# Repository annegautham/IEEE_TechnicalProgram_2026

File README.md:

View this project on [CADLAB.io](https://cadlab.io/project/30137). 

# IEEE_TechnicalProgram_2026

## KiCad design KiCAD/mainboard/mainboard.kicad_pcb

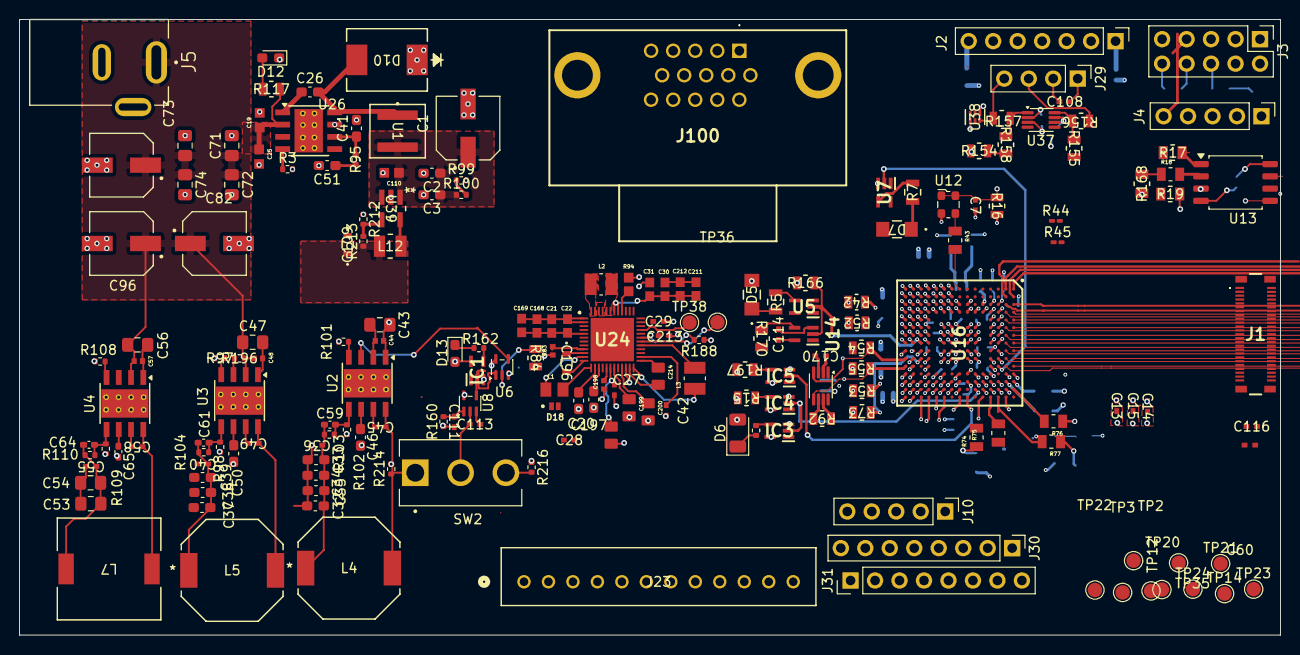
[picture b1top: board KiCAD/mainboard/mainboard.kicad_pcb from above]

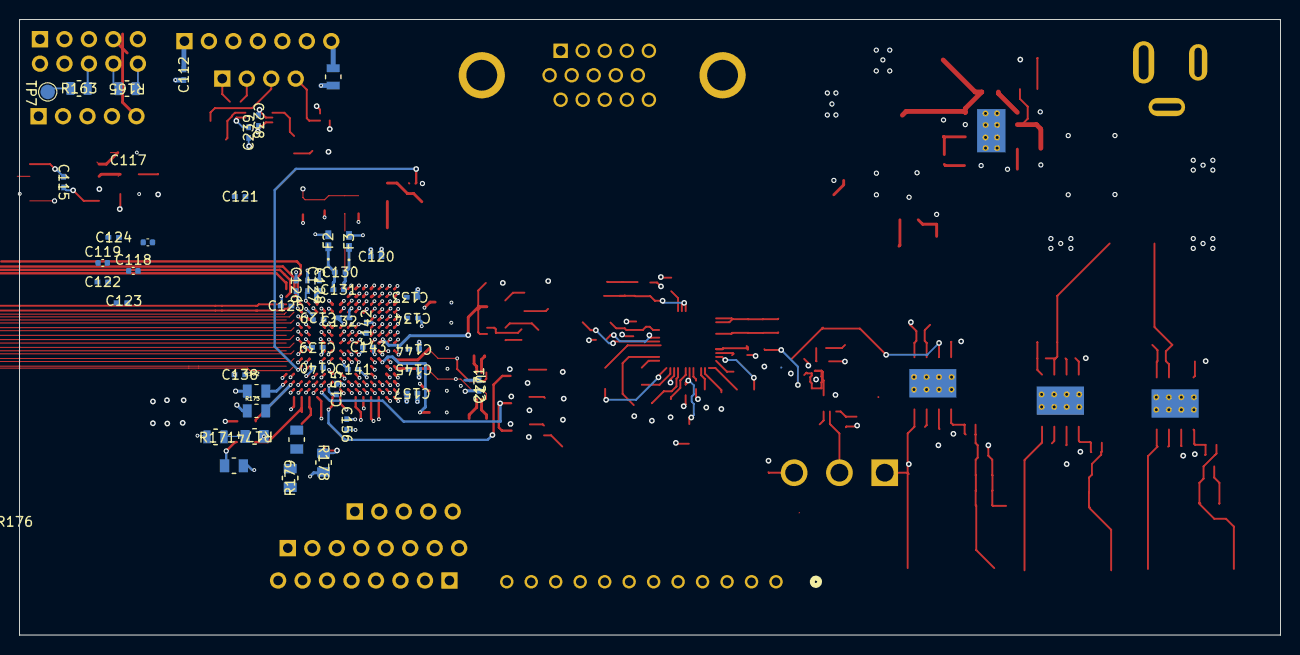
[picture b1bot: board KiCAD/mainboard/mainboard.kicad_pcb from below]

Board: 10 copper layers, 130.9 x 63.9 mm, 240 parts (48 on the bottom side), 171 nets.

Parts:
C1, C82, C83, C96: 100 uF; CAP_EEEFT1V101AP
C2, C3, C41: 12pF; C_0603_1608Metric_Pad1.08x0.95mm_HandSolder
C7, C13, C14, C15, C27, C29, C42, C116, C120, C121, C122, C123, C124, C125, C126, C128, C129, C130, C131, C132, C133, C134, C139, C140, C141, C142, C143, C144, C145, C155, C156, C157, C213, C238, C239: 100nF; CAP_CL05_SAM
C19, C25, C110: 4.7uF; GRM188C81E475KE11D
C20, C197: 220nF; C_0603_1608Metric_Pad1.08x0.95mm_HandSolder
C21, C22, C30, C31, C168, C169, C211, C212: 22uF; CAPC1608X100N
C26: 100nF; C_0603_1608Metric_Pad1.08x0.95mm_HandSolder
C28: 4.7uF; CAP_CL05_SAM
C32, C33, C34, C35, C37, C38, C39: 22uF; C_0603_1608Metric_Pad1.08x0.95mm_HandSolder
C36, C40, C45, C49, C55, C58, C60, C111, C113: 100nF; ul_CL05B104KO5NNNC
C43, C47, C56: 4.7uF; C_0805_2012Metric_Pad1.18x1.45mm_HandSolder
C44, C48, C57, C198: 220nF; GRM155R6YA224KE01D
C46, C50: 1uF; C_0603_1608Metric_Pad1.08x0.95mm_HandSolder
C51: 100pF; C_0603_1608Metric_Pad1.08x0.95mm_HandSolder
C53, C54: 10uF; C_0805_2012Metric_Pad1.18x1.45mm_HandSolder
C59: 4.7pF; C_0402_1005Metric_Pad0.74x0.62mm_HandSolder
C61: 10pF; C_0402_1005Metric_Pad0.74x0.62mm_HandSolder
C64: 18pF; C_0402_1005Metric_Pad0.74x0.62mm_HandSolder
C65: 1uF; C_0402_1005Metric_Pad0.74x0.62mm_HandSolder
C71, C72, C73, C74: 10 uF; C_0805_2012Metric_Pad1.18x1.45mm_HandSolder
C108, C112, C114, C115, C127, C138, C170, C171: 100n; CAP_CL05_SAM
C109, C196: 10uF; C1608X5R1A106M080AC
C117, C118, C119: 220n; C_0402_1005Metric
C199: 2.2uF; CAPC2012X135N
C200, C201, C214: 1uF; CAPC2012X135N
D5, D7: SML-LX1206SIC-TR; LED_SML-LX1206SIC-TR_LUM-M
D6: LED; LED_1206_3216Metric
D10: B560C; SMC_DIO
D12, D13: LED; LED_0603_1608Metric_Pad1.05x0.95mm_HandSolder
D18: D_Schottky; DIO_PESD5V0S1UL_315
F2, F3: 1500mA; BLM15P_FBD-M
IC1, IC3: SN74AUP1G06DCKR; SOT65P210X110-5N
IC4, IC5: SN74AUP1G07DCKR; SOT65P210X110-5N
J1: AXT550124
J2: Conn_01x07_Pin; PinHeader_1x07_P2.54mm_Vertical
J3: Conn_02x05_Odd_Even; PinHeader_2x05_P2.54mm_Vertical
J4, J10: Conn_01x05_Pin; PinHeader_1x05_P2.54mm_Vertical
J5: EJ508B; MPD_EJ508B
J23: B12B-XH-ALFSN; B12B-XH-A-LF-SN-
J29: Conn_01x04_Pin; PinHeader_1x04_P2.54mm_Vertical
J30, J31: Conn_01x08_Pin; PinHeader_1x08_P2.54mm_Vertical
J100: AHDF15A-KG-TAXB; AHDF15AKGTAXB
L1: 10uH; INDC2012X100N
L2, L3: 2.2uH; INDC2520X100N
L4, L5: SRU1038-3R5Y; IND_BOURNS_SRU1038
L7: DR1040-5R2-R; DR1040
L12: LQM2HPN2R2MG0L; IND_LQM2HPN2R2MG0L_MUR
R3, R212: 78.7k; R_0402_1005Metric
R5, R7: 100; RES_CRCW_0805
R6: 150; R_0402_1005Metric
R15, R84, R92, R155, R158, R163, R164, R165, R166, R170, R197: 10k; STA_RMCF0805_STP
R16, R154, R156, R157, R171: 0; RES_R-070RL_VIS
R17, R19, R168, R174, R176, R177, R178, R179: 100k; RES_RMCF0805_STP
R18, R43, R74, R75, R76, R77, R172, R173: 30.1; RESC2012X60N
R42, R52: 7.87k; RES_RM10_CCE
R44, R45: 43; R_0201_0603Metric_Pad0.64x0.40mm_HandSolder
R53, R54, R55, R73, R117: 3.3k; RES_ERJP06_PAN
R83: 30.1; RESC1005X40N
R94: 39m; RESC1608X60N
R95, R99, R100: 22.1k; R_0402_1005Metric
R97, R101, R108, R160, R196, R214, R216: 10k; R_0402_1005Metric
R98: 124k; R_0402_1005Metric
R102: 499k; R_0402_1005Metric
R103, R104, R110, R188: 100k; R_0402_1005Metric
R109: 43.2k; R_0402_1005Metric
R162: 200; R_0402_1005Metric
R213: 360k; R_0402_1005Metric
SW2: 100SP1T1B4M2QE; SW_100SP1T1B4M2QE
TP2, TP3, TP7, TP12, TP14, TP20, TP21, TP22, TP35: TestPoint; TestPoint_Pad_D1.5mm
TP23: VOFS; TestPoint_Pad_D1.5mm
TP24: VBIAS; TestPoint_Pad_D1.5mm
TP36: SENS2; TestPoint_Pad_D1.5mm
TP38: SENS1; TestPoint_Pad_D1.5mm
U1: XAL5030-472MEC; XAL5030-472MEC_COC
U2, U3, U4: LMR33610BDDAR; Texas_HSOP-8-1EP_3.9x4.9mm_P1.27mm_ThermalVias
U5, U7, U14: SN74AUP1G06DCKR; SOT65P210X110-5N
U6: 74AHC1G08; SOT-353_SC-70-5
U8: 74AHC1G32; SOT-353_SC-70-5
U12: ECS-2520MV-xxx-xx; Oscillator_SMD_ECS_2520MV-xxx-xx-4Pin_2.5x2.0mm
U13: MX25L3233FM2; SOIC-8_5.3x5.3mm_P1.27mm
U16: DLPC1438ZEZ; BGA201C80P15X15_1300X1300X100
U22, U37: TXS0102DCU; VSSOP-8_2.3x2mm_P0.5mm
U24: DLPA2005ERSLT; QFN40P600X600X100-49N-D
U26: TPS54340DDA; TI_SO-PowerPAD-8_ThermalVias
U38: TPD2E001DRYR; DRY6
U39: TPS62260DDCT; DDC5

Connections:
/DLPA2005_Interface/<NO NET>: L1.1, U24.13 (SWP)
/DLPA2005_Interface/L1: L2.2, U24.47 (L1_1), U24.48 (L1_2)
/DLPA2005_Interface/L2: L2.1, U24.43 (L2_1), U24.44 (L2_2)
/DLPA2005_Interface/LED_ANODE: C30.1, C31.1, C211.1, C212.1, U24.41 (VLED_1), U24.42 (VLED_2)
/DLPA2005_Interface/LED_SEL_1: R171.2, R174.2, TP21.1 (1_1), U24.34 (LED_SEL1)
/DLPA2005_Interface/PMIC_SPI_DOUT: R83.1, U24.9 (SPI_DOUT)
/DLPA2005_Interface/PROJ_ON: IC1.2 (A), U6.1, U8.4, U16.G14 (GPIO_08), U24.27 (PROJ_ON)
/DLPA2005_Interface/PWM_IN: C42.2, U24.26 (PWM_IN)
/DLPA2005_Interface/RLIM: R94.1, U24.36 (RLIM_K), U24.40 (RLIM)
/DLPA2005_Interface/SENS2: TP36.1 (1_1), U24.30 (SENS2)
/DLPA2005_Interface/SENS!: TP38.1 (1_1), U24.33 (SENS1)
/DLPA2005_Interface/SWC: L3.1, U24.24 (SWC)
/DLPA2005_Interface/SWN: L1.2, U24.11 (SWN)
/DLPA2005_Interface/VRST: C13.2, C20.1, C124.2, J1.45, TP22.1 (1_1), U24.14 (CNTR_VRST)
/DLPC1438_Interface/CMP_OUT: U16.A12 (CMP_OUT), U24.28 (CMP_OUT)
/DLPC1438_Interface/DATEN_CM_D: J100.12, U16.P2 (DATEN_CM_D)
/DLPC1438_Interface/DLPC_3DR: R52.1, U16.N6 (3DR)
/DLPC1438_Interface/DLPC_FLSH_PROG: R163.1, TP7.1 (1_1)
/DLPC1438_Interface/DLPC_HOST_IRQ: R166.2, U5.2 (A), U14.2 (A), U16.N8 (HOST_IRQ)
/DLPC1438_Interface/DLPC_LED_SEL_0: TP20.1 (1_1), U16.B15 (LED_SEL_0)
/DLPC1438_Interface/DLPC_LED_SEL_1: R171.1, U16.B14 (LED_SEL_1)
/DLPC1438_Interface/DLPC_PLLO: TP14.1 (1_1), U16.J1 (PLL_REFCL_K_O)
/DLPC1438_Interface/DLPC_SPICLK: R172.2, U16.A13 (SPI0_CLK)
/DLPC1438_Interface/DLPC_SPICSZ0: R76.2, U16.A14 (SPI0_CSZ0)
/DLPC1438_Interface/DLPC_SPIDOUT: R173.2, U16.B13 (SPI0_DOUT)
/DLPC1438_Interface/DMD_DEN_ARSTZ: J1.4, U16.B1 (DMD_DEN__ARSTZ)
/DLPC1438_Interface/DMD_HS_CLK_N: J1.14, U16.B7 (DMD_HS_CLK__N)
/DLPC1438_Interface/DMD_HS_CLK_P: J1.13, U16.A7 (DMD_HS_CLK__P)
/DLPC1438_Interface/DMD_HS_WDATAA_N: J1.19, U16.B11 (DMD_HS_W_DATAA_N)
/DLPC1438_Interface/DMD_HS_WDATAA_P: J1.18, U16.A11 (DMD_HS_W_DATAA_P)
/DLPC1438_Interface/DMD_HS_WDATAB_N: J1.17, U16.B10 (DMD_HS_W_DATAB_N)
/DLPC1438_Interface/DMD_HS_WDATAB_P: J1.16, U16.A10 (DMD_HS_W_DATAB_P)
/DLPC1438_Interface/DMD_HS_WDATAC_N: J1.32, U16.B9 (DMD_HS_W_DATAC_N)
/DLPC1438_Interface/DMD_HS_WDATAC_P: J1.33, U16.A9 (DMD_HS_W_DATAC_P)
/DLPC1438_Interface/DMD_HS_WDATAD_N: J1.34, U16.B8 (DMD_HS_W_DATAD_N)
/DLPC1438_Interface/DMD_HS_WDATAD_P: J1.35, U16.A8 (DMD_HS_W_DATAD_P)
/DLPC1438_Interface/DMD_HS_WDATAE_N: J1.40, U16.B6 (DMD_HS_W_DATAE_N)
/DLPC1438_Interface/DMD_HS_WDATAE_P: J1.41, U16.A6 (DMD_HS_W_DATAE_P)
/DLPC1438_Interface/DMD_HS_WDATAF_N: J1.42, U16.B5 (DMD_HS_W_DATAF_N)
/DLPC1438_Interface/DMD_HS_WDATAF_P: J1.43, U16.A5 (DMD_HS_W_DATAF_P)
/DLPC1438_Interface/DMD_HS_WDATAG_N: J1.11, U16.B4 (DMD_HS_W_DATAG_N)
/DLPC1438_Interface/DMD_HS_WDATAG_P: J1.10 (19), U16.A4 (DMD_HS_W_DATAG_P)
/DLPC1438_Interface/DMD_HS_WDATAH_N: J1.9, U16.B3 (DMD_HS_W_DATAH_N)
/DLPC1438_Interface/DMD_HS_WDATAH_P: J1.8, U16.A3 (DMD_HS_W_DATAH_P)
/DLPC1438_Interface/DMD_LS_RDATA: J1.3, U16.B2 (DMD_LS_R_DATA)
/DLPC1438_Interface/EXT_I2CPWR: C108.2, J29.1
/DLPC1438_Interface/EXT_SCL: J29.3, R156.1
/DLPC1438_Interface/EXT_SCL_T: R155.1, R156.2, U37.8 (B1)
/DLPC1438_Interface/EXT_SDA: J29.4, R157.1, U38.3 (IO1)
/DLPC1438_Interface/EXT_SDA_T: R157.2, R158.1, U37.1 (B2)
/DLPC1438_Interface/FPGA_RDY: J23.12, U16.K14 (GPIO_14)
/DLPC1438_Interface/GPIO_1: R77.2, U16.C15 (GPIO_01)
/DLPC1438_Interface/GPIO_2: R74.2, U16.D14 (GPIO_02)
/DLPC1438_Interface/GPIO_3: R75.2, R177.2, U16.D15 (GPIO_03)
/DLPC1438_Interface/GPIO_4: J30.1, U16.E14 (GPIO_04)
/DLPC1438_Interface/GPIO_5: J30.2, U16.E15 (GPIO_05)
/DLPC1438_Interface/GPIO_12: J30.3, U16.J14 (GPIO_12)
/DLPC1438_Interface/GPIO_15: J30.4, U16.K15 (GPIO_15)
/DLPC1438_Interface/GPIO_16: J30.5, U16.L14 (GPIO_16)
/DLPC1438_Interface/GPIO_17: J30.6, U16.L15 (GPIO_17)
/DLPC1438_Interface/GPIO_18: J30.7, U16.M14 (GPIO_18)
/DLPC1438_Interface/GPIO_19: J30.8, U16.M15 (GPIO_19)
/DLPC1438_Interface/HOST_IR: J23.5, R170.1, U14.4 (Y)
/DLPC1438_Interface/HSYNC: J100.11, U16.N5 (HSYNC_CS)
/DLPC1438_Interface/I2C1_33_EN: R92.2, U22.6 (OE)
/DLPC1438_Interface/IIC0_SCL: J23.7, R73.1, U16.N10 (IIC0_SCL), U37.5 (A1)
/DLPC1438_Interface/IIC0_SDA: J23.6, R53.1, U16.N9 (IIC0_SDA), U37.4 (A2)
/DLPC1438_Interface/IIC1_SCL: J100.13, U22.8 (B1)
/DLPC1438_Interface/IIC1_SCL_1p8: R55.1, U16.R11 (IIC1_SCL), U22.5 (A1)
/DLPC1438_Interface/IIC1_SDA: J100.14, U22.1 (B2)
/DLPC1438_Interface/IIC1_SDA_1p8: R54.1, U16.R10 (IIC1_SDA), U22.4 (A2)
/DLPC1438_Interface/INTZ: R84.1, U6.2, U16.C13 (PARKZ), U24.6 (INTZ)
/DLPC1438_Interface/JTAG_TCK: J2.3, U16.P12 (JTAGTCK)
/DLPC1438_Interface/JTAG_TDI: J2.5, U16.P13 (JTAGTDI)
/DLPC1438_Interface/JTAG_TDO: J2.4, U16.N13 (JTAGTDO1)
/DLPC1438_Interface/JTAG_TMS: J2.6, U16.M13 (JTAGTMS1)
/DLPC1438_Interface/JTAG_TRSTZ: J2.7, R164.2, U16.P11 (JTAGTRSTZ)
/DLPC1438_Interface/LS_CLK: J1.6, R45.1, R45.2, U16.A1 (DMD_LS_C_LK)
/DLPC1438_Interface/LS_WDATA: J1.5, R44.1, R44.2, U16.A2 (DMD_LS_W_DATA)
/DLPC1438_Interface/OSC_OUT: R43.2, U16.H1 (PLL_REFCL_K_I)
/DLPC1438_Interface/OSC_OUT_T: R43.1, TP12.1 (1_1), U12.3 (OUT)
/DLPC1438_Interface/PCLK: J100.9, U16.P3 (PCLK)
/DLPC1438_Interface/PDATA0: J100.1, U16.K2 (PDATA_0)
/DLPC1438_Interface/PDATA1: J100.2, U16.K1 (PDATA_1)
/DLPC1438_Interface/PDATA2: J100.3, U16.L2 (PDATA_2)
/DLPC1438_Interface/PDATA3: J100.4, U16.L1 (PDATA_3)
/DLPC1438_Interface/PDATA4: J100.5, U16.M2 (PDATA_4)
/DLPC1438_Interface/PDATA5: J100.6, U16.M1 (PDATA_5)
/DLPC1438_Interface/PDATA6: J100.7, U16.N2 (PDATA_6)
/DLPC1438_Interface/PDATA7: J100.8, U16.N1 (PDATA_7)
/DLPC1438_Interface/PDM_CVS_TE: R42.1, U16.N4 (PDM_CVS__TE)
/DLPC1438_Interface/RESETZ: U7.2 (A), U16.C11 (RESETZ), U24.4 (RESETZ)
/DLPC1438_Interface/RSTZ_LED: D7.1, R7.1
/DLPC1438_Interface/RSTZ_LED_OUT: R7.2, U7.4 (Y)
/DLPC1438_Interface/SPI0_5V: J3.4, J3.6, R163.2
/DLPC1438_Interface/SPI0_CLK: J3.7, J4.5, R19.2, R172.1, U13.6 (SCLK)
/DLPC1438_Interface/SPI0_CSZ0: J3.9, J4.4, R17.2, R76.1, U13.1 (~CS)
/DLPC1438_Interface/SPI0_MISO: J3.5, J4.2, R18.1, R168.2, U16.B12 (SPI0_DIN)
/DLPC1438_Interface/SPI0_MISO_T: R18.2, U13.2 (SO/SIO1)
/DLPC1438_Interface/SPI0_MOSI: J3.8, J4.3, R165.2, R173.1, U13.5 (SI/SIO0)
/DLPC1438_Interface/SPI1_CLK: J10.5, R77.1, R176.1, U24.7 (SPI_CLK)
/DLPC1438_Interface/SPI1_CSZ0: J10.4, R75.1, U24.8 (SPI_CSZ)
/DLPC1438_Interface/SPI1_MISO: J10.2, R83.2, R179.1, U16.C14 (GPIO_00)
/DLPC1438_Interface/SPI1_MOSI: J10.3, R74.1, R178.1, U24.3 (SPI_DIN)
/DLPC1438_Interface/TSTPT_0: J31.1, U16.R12 (TSTPT_0)
/DLPC1438_Interface/TSTPT_1: J31.2, U16.R13 (TSTPT_1)
/DLPC1438_Interface/TSTPT_2: J31.3, U16.R14 (TSTPT_2)
/DLPC1438_Interface/TSTPT_3: J31.4, U16.R15 (TSTPT_3)
/DLPC1438_Interface/TSTPT_4: J31.5, U16.P14 (TSTPT_4)
/DLPC1438_Interface/TSTPT_5: J31.6, U16.P15 (TSTPT_5)
/DLPC1438_Interface/TSTPT_6: J31.7, U16.N14 (TSTPT_6)
/DLPC1438_Interface/TSTPT_7: J31.8, U16.N15 (TSTPT_7)
/DLPC1438_Interface/VDD_PLL: C130.2, C131.2, F3.1, U16.H2 (VDD_PLLM), U16.J2 (VDD_PLLD)
/DLPC1438_Interface/VOSC: C7.1, R16.1, U12.1 (Tri-State), U12.4 (VDD)
/DLPC1438_Interface/VSS_PLL: C130.1, C131.1, F2.1, U16.G3 (VSS_PLLM), U16.H3 (VSS_PLLD)
/DLPC1438_Interface/VSYNC: J100.10, U16.P1 (VSYNC_WE)
/DMD_Interface/PRINT_ACTIVE: IC5.4 (Y), R197.1
/DMD_Interface/SYS_RDY: IC4.4 (Y), J23.10, R15.1
/DMD_Interface/SYS_RDY_LED: D6.1 (K), R6.1
/DMD_Interface/SYS_RDY_LED_DRV: IC3.4 (Y), R6.2
/FPGA_Connections/FE_PROJ_ON: C111.1, J23.8, R160.2, U8.1
/Power_Input&Generation/FPGA_PWREN: U2.3 (EN), U4.3 (EN), U6.4
/Power_Input&Generation/P1P2V_BOOT: C45.2, U2.7 (BOOT)
/Power_Input&Generation/P1P2V_FB: C59.2, R102.1, R103.2, U2.5 (FB)
/Power_Input&Generation/P1P2V_PG: R101.1, U2.4 (PG)
/Power_Input&Generation/P1P2V_SW: C45.1, L4.2, U2.8 (SW)
/Power_Input&Generation/P1P2V_VCC: C46.1, U2.6 (VCC)
/Power_Input&Generation/P1P8V_BOOT: C49.2, U3.7 (BOOT)
/Power_Input&Generation/P1P8V_EN: R196.2, U3.3 (EN)
/Power_Input&Generation/P1P8V_FB: C61.2, R98.1, R104.2, U3.5 (FB)
/Power_Input&Generation/P1P8V_PG: R97.1, U3.4 (PG)
/Power_Input&Generation/P1P8V_SW: C49.1, L5.2, U3.8 (SW)
/Power_Input&Generation/P1P8V_VCC: C50.1, U3.6 (VCC)
/Power_Input&Generation/P3P3V_BOOT: C58.2, U4.7 (BOOT)
/Power_Input&Generation/P3P3V_FB: C64.2, R109.1, R110.2, U4.5 (FB)
/Power_Input&Generation/P3P3V_PG: R108.1, U4.4 (PG)
/Power_Input&Generation/P3P3V_SW: C58.1, L7.1, U4.8 (SW)
/Power_Input&Generation/P3P3V_VCC: C65.1, U4.6 (VCC)
/Power_Input&Generation/PROJ_ON_DRV: IC1.4 (Y), R162.2
/Power_Input&Generation/SW_PROJ_ON: C113.1, SW2.2, U8.2
EXT_VIN: C19.1, C25.1, C43.1, C44.1, C47.1, C48.1, C56.1, C57.1, C71.1, C72.1, C73.1, C74.1, C82.1, C83.1, C96.1, J5.1, R117.2, R196.1, U2.2 (VIN), U3.2 (VIN), U4.2 (VIN), U26.2 (VIN)
GND: C1.2, C2.2, C3.2, C7.2, C13.1, C14.1, C15.1, C19.2, C20.2, C21.2, C22.2, C25.2, C27.2, C28.1, C29.2, C30.2, C31.2, C32.2, C33.2, C34.2, C35.2, C36.2, C37.2, C38.2, C39.2, C40.2, C41.2, C42.1, C43.2, C44.2, C46.2, C47.2, C48.2, C50.2, C51.2, C53.2, C54.2, C55.2, C56.2, C57.2, C60.2, C65.2, C71.2, C72.2, C73.2, C74.2, C82.2, C83.2, C96.2, C108.1, C109.2, C110.2, C111.2, C112.1, C113.2, C114.2, C115.2, C116.1, C117.2, C118.2, C119.2, C120.1, C121.1, C122.1, C123.1, C124.1, C125.1, C126.1, C127.1, C128.1, C129.1, C132.1, C133.1, C134.1, C138.1, C139.1, C140.1, C141.1, C142.1, C143.1, C144.1, C145.1, C155.1, C156.1, C157.1, C168.2, C169.2, C170.1, C171.2, C196.2, C197.1, C198.1, C199.2, C200.2, C201.2, C211.2, C212.2, C213.2, C214.2, C238.1, C239.1, D10.1 (A), D12.1 (K), F2.2, IC1.3 (GND), IC3.3 (GND), IC4.3 (GND), IC5.3 (GND), J1.2, J1.7, J1.12, J1.15, J1.20, J1.21, J1.22, J1.25 (49), J1.26, J1.30, J1.31, J1.36, J1.39, J1.44, J1.48, J1.49, J1.51 (MP1), J1.52 (MP2), J1.53 (MP3), J1.54 (MP4), J2.2, J3.2, J3.10, J4.1, J5.3, J10.1, J23.1, J29.2, J100.15, R3.2, R19.1, R42.2, R52.2, R94.2, R98.2, R99.2, R102.2, R109.2, R160.1, R164.1, R165.1, R168.1, R174.1, R176.2, R178.2, R179.2, R188.1, R212.1, R214.2, U2.1 (GND), U2.9 (GND), U3.1 (GND), U3.9 (GND), U4.1 (GND), U4.9 (GND), U5.3 (GND), U6.3 (GND), U7.3 (GND), U8.3 (GND), U12.2 (GND), U13.4 (GND), U14.3 (GND), U16.C4 (VSS_1), U16.C6 (VSS_2), U16.C8 (VSS_3), U16.C10 (HWTEST_E_N), U16.D6 (VSS_4), U16.D8 (VSS_5), U16.D10 (VSS_6), U16.E4 (VSS_7), U16.E13 (VSS_8), U16.F4 (VSS_9), U16.F6 (VSS_10), U16.F7 (VSS_11), U16.F8 (VSS_12), U16.F9 (VSS_13), U16.F10 (VSS_14), U16.G4 (VSS_15), U16.G6 (VSS_16), U16.G7 (VSS_17), U16.G8 (VSS_18), U16.G9 (VSS_19), U16.G10 (VSS_20), U16.G12 (VSS_21), U16.G13 (VSS_22), U16.H4 (VSS_23), U16.H6 (VSS_24), U16.H7 (VSS_25), U16.H8 (VSS_26), U16.H9 (VSS_27), U16.H10 (VSS_28), U16.H12 (VSS_29), U16.J3 (VSS_30), U16.J6 (VSS_31), U16.J7 (VSS_32), U16.J8 (VSS_33), U16.J9 (VSS_34), U16.J10 (VSS_35), U16.J13 (VSS_36), U16.K4 (VSS_37), U16.K6 (VSS_38), U16.K7 (VSS_39), U16.K8 (VSS_40), U16.K9 (VSS_41), U16.K10 (VSS_42), U16.K12 (VSS_43), U16.L3 (VSS_44), U16.M4 (VSS_45), U16.M5 (VSS_46), U16.M8 (VSS_47), U16.M12 (VSS_48), U16.P4 (PDATA_11), U16.P5 (PDATA_13), U16.P6 (PDATA_15), U16.P7 (PDATA_17), U16.P8 (PDATA_19), U16.P9 (PDATA_21), U16.P10 (PDATA_23), U16.R1 (PDATA_8), U16.R2 (PDATA_9), U16.R3 (PDATA_10), U16.R4 (PDATA_12), U16.R5 (PDATA_14), U16.R6 (PDATA_16), U16.R7 (PDATA_18), U16.R8 (PDATA_20), U16.R9 (PDATA_22), U22.2 (GND), U24.5 (AGND1), U24.12 (PGNDR), U24.20 (GND), U24.23 (PGNDC), U24.45 (PGNDL_1), U24.46 (PGNDL_2), U24.49 (EP), U26.7 (GND), U26.9 (GNDPAD), U37.2 (GND), U38.4 (GND), U39.2 (GND)
GPIO_6: IC3.2 (A), IC4.2 (A), U16.F14 (GPIO_06)
GPIO_9: IC5.2 (A), U16.G15 (GPIO_09)
unnamed: C51.1, R95.2
unnamed: D5.1, R5.1
unnamed: C26.2, D10.2 (C), U1.1, U26.8 (SW)
unnamed: D12.2 (A), R117.1
unnamed: D13.1 (K), R162.1
unnamed: R99.1, R100.2
unnamed: R214.1, SW2.1
unnamed: R216.2, SW2.3
unnamed: R5.2, U5.4 (Y)
unnamed: R188.2, U24.31 (LED_SEL0)
unnamed: C200.1, TP2.1 (1_1), U24.21 (LS_OUT)
unnamed: C26.1, U26.1 (BOOT)
unnamed: C41.1, R95.1, U26.6 (COMP)
unnamed: R3.1, U26.4 (RT/CLK)
unnamed: R212.2, R213.2, U39.4 (FB)
unnamed: L12.2, U39.5 (SW)
P1P1V: C28.2, C120.2, C125.2, C126.2, C127.2, C128.2, C132.2, C139.2, C140.2, C141.2, C142.2, C143.2, C155.2, F3.2, L3.2, TP35.1 (1_1), U16.C3 (VDDLP12), U16.C5 (VDD_1), U16.D3 (VDD_2), U16.D5 (VDD_3), U16.D7 (VDD_4), U16.D9 (VDD_5), U16.D12 (VDD_6), U16.D13 (VDD_7), U16.E3 (VDD_8), U16.F13 (VDD_9), U16.H13 (VDD_10), U16.J4 (VDD_11), U16.J12 (VDD_12), U16.K3 (VDD_13), U16.L4 (VDD_14), U16.L12 (VDD_15), U16.L13 (VDD_16), U16.M6 (VDD_17), U16.M9 (VDD_18), U16.M10 (VDD_19), U24.29 (VCORE)
P1P2V: C32.1, C33.1, C34.1, C35.1, C36.1, C59.1, L4.1, R103.1
P1P8V: C37.1, C38.1, C39.1, C40.1, C61.1, C238.2, L5.1, R104.1, U24.22 (LS_IN), U37.3 (VCCA)
P1P8V_DLPC: C60.1, C112.2, C114.1, C116.2, C117.1, C118.1, C119.1, C121.2, C129.2, C133.2, C134.2, C144.2, C145.2, C156.2, C157.2, C170.2, C213.1, IC3.5 (VCC), IC4.5 (VCC), IC5.5 (VCC), J1.1, J1.37, J1.38, J1.50, J2.1, R16.2, R53.2, R54.2, R55.2, R73.2, R166.1, R177.1, TP3.1 (1_1), U5.5 (VCC), U7.5 (VCC), U14.5 (VCC), U16.C7 (VCC_1), U16.C9 (VCC_2), U16.D4 (VCC_3), U16.E12 (VCC_4), U16.F12 (VCC_5), U16.K13 (VCC_6), U16.M3 (VCC_INTF_1), U16.M7 (VCC_INTF_2), U16.M11 (VCC_7), U16.N3 (VCC_INTF_3), U16.N7 (VCC_INTF_4), U22.3 (VCCA), U24.32 (VSPI)
P3P3V: C53.1, C54.1, C55.1, C64.1, C171.1, D5.2, D6.2 (A), D7.2, L7.2, R15.2, R92.1, R110.1, R170.2, R197.2, U22.7 (VCCB)
P3P3V_SB: C109.1, C115.1, C138.2, D13.2 (A), IC1.5 (VCC), L12.1, R17.1, R84.2, R97.2, R101.2, R108.2, R154.1, R213.1, R216.1, U6.5 (VCC), U8.5 (VCC), U13.3 (~WP/SIO2), U13.7 (~HOLD/SIO3), U13.8 (VCC), U16.D11 (VCC_FLSH)
P5V: C1.1, C2.1, C3.1, C21.1, C22.1, C27.1, C110.1, C168.1, C169.1, C196.1, C201.1, C214.1, R100.1, U1.2, U24.1 (VINL_1), U24.2 (VINL_2), U24.10 (VINR), U24.18 (VINA), U24.25 (VINC), U38.1 (VCC), U39.1 (VIN), U39.3 (EN)
V2V5: C199.1, U24.19 (V2V5)
V6V: C29.1, U24.35 (V6V)
VBIAS: C14.2, C123.2, C197.2, J1.46, TP24.1 (1_1), U24.15 (VBIAS)
VOFS: C15.2, C122.2, C198.2, J1.47, TP23.1 (1_1), U24.17 (VOFS)

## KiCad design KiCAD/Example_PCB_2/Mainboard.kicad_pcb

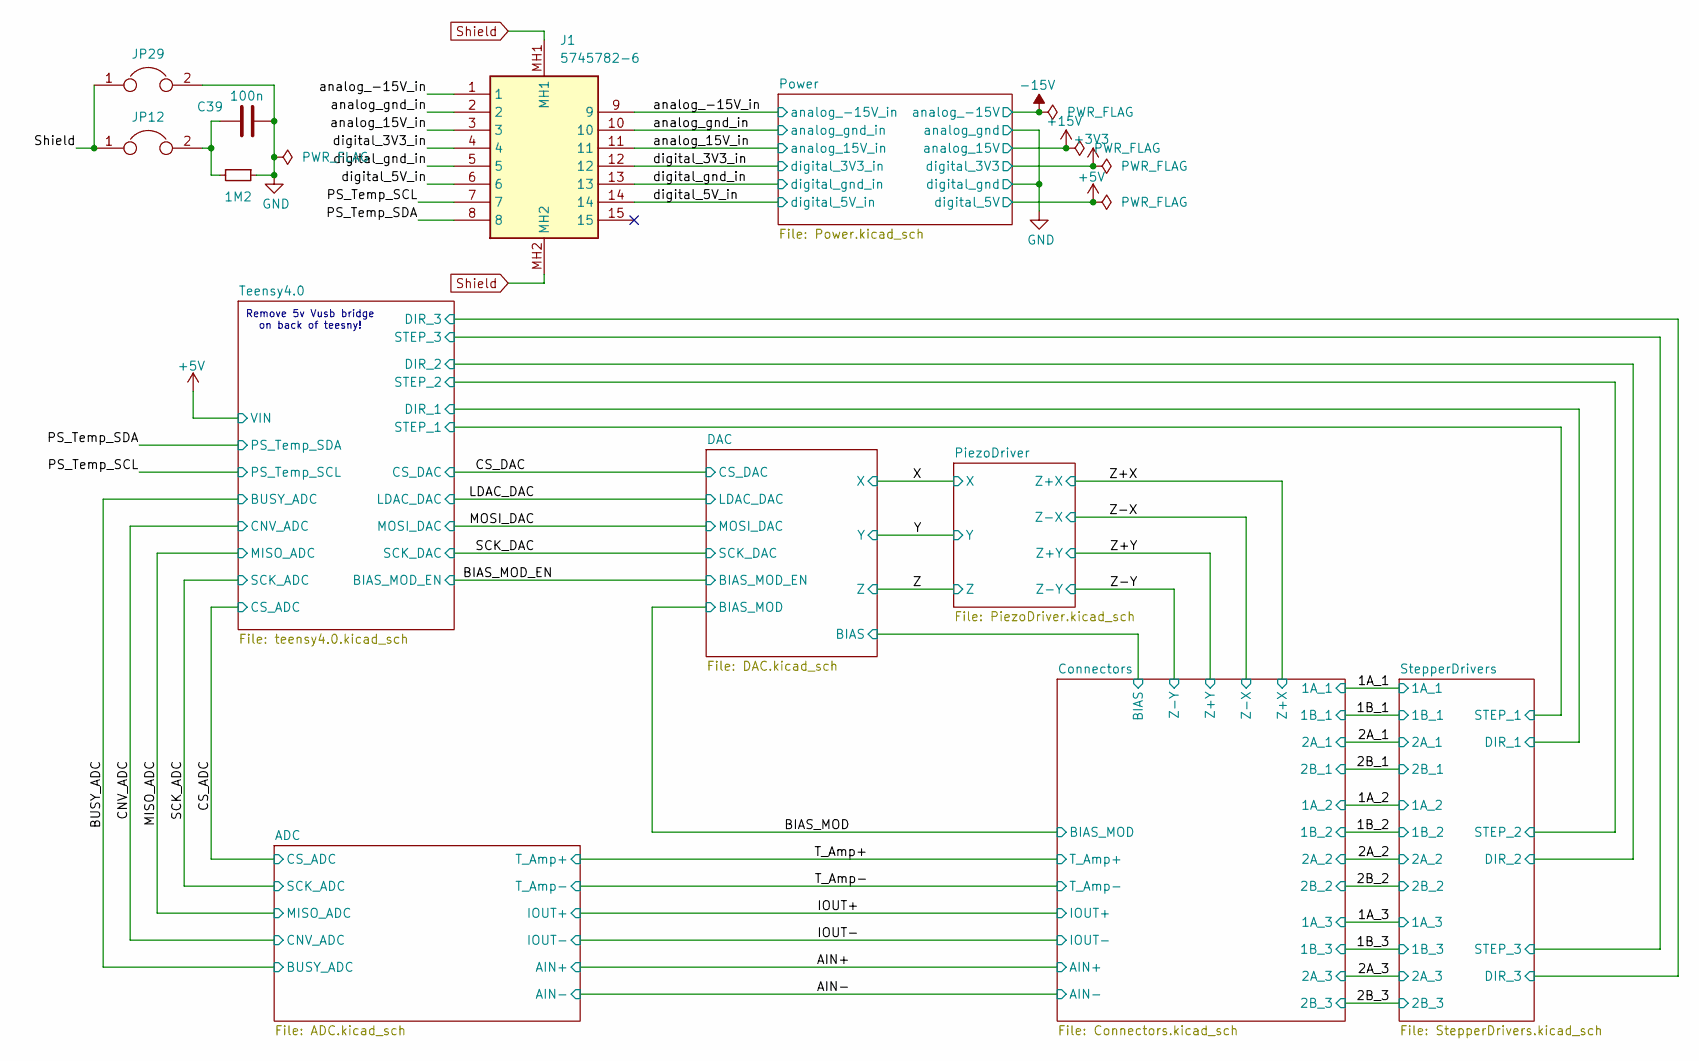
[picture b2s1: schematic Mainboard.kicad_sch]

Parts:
C39: 100n; C_0805_2012Metric; Mouser Part Number 80-C0805S104K1RACAUT; LCSC C14663
J1: 5745782-6; 57457826; Mouser Part Number 571-5745782-6
JP12, JP29: Jumper; SolderJumper-2_P1.3mm_Open_TrianglePad1.0x1.5mm
R30: 1M2; R_0805_2012Metric; Mouser Part Number 755-SDR10EZPF1204; LCSC C22107

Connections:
+3V3: J1.4, J1.12; also elsewhere on the board
+5V: J1.6, J1.14; also elsewhere on the board
+15V: J1.3, J1.11; also elsewhere on the board
-15V: J1.1, J1.9; also elsewhere on the board
/PS_Temp_SCL: J1.7; also elsewhere on the board
/PS_Temp_SDA: J1.8; also elsewhere on the board
GND: C39.2, J1.2, J1.5, J1.10, J1.13, JP29.2, R30.1; also elsewhere on the board
unnamed: C39.1, JP12.2, R30.2
Shield: J1.MH1, J1.MH2, JP12.1, JP29.1; also elsewhere on the board

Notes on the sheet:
Remove 5v Vusb bridge on back of teesny!

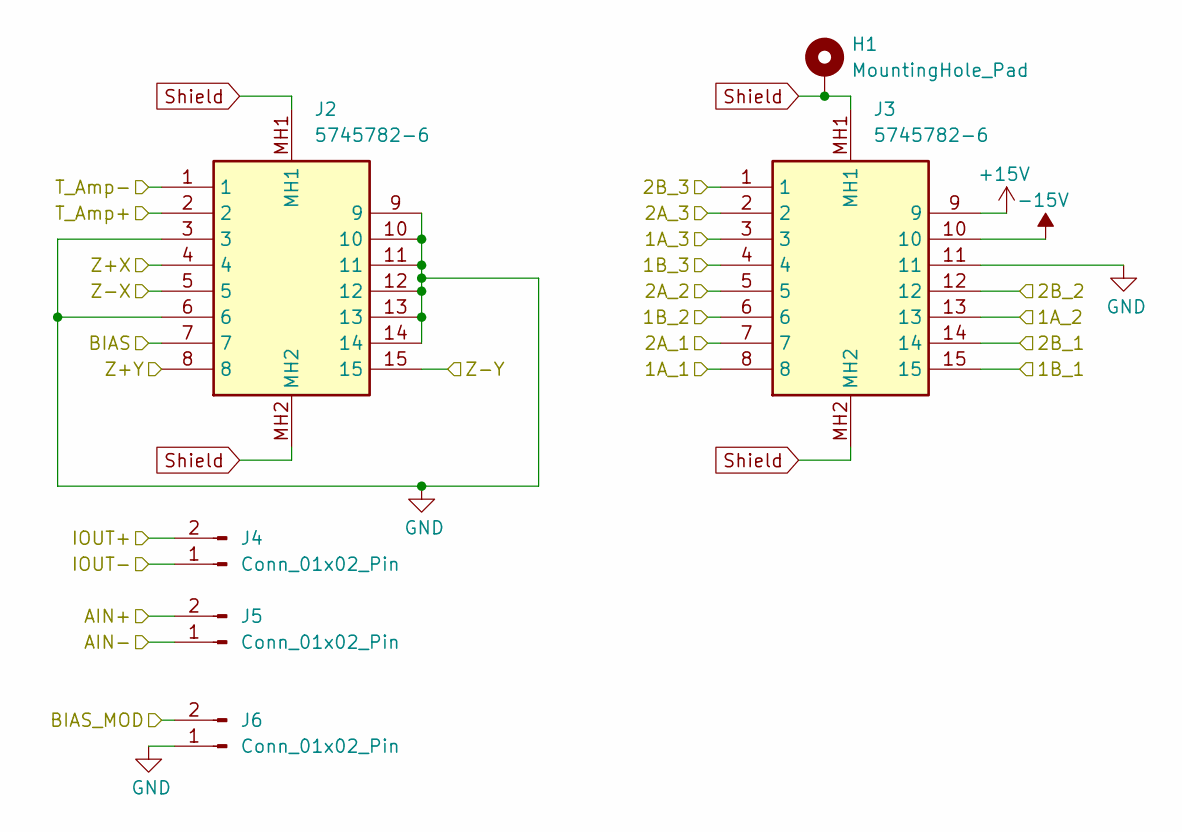
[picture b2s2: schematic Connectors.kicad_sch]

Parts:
H1: MountingHole_Pad; MountingHole_2.2mm_M2_Pad_Via
J2, J3: 5745782-6; 57457826; Mouser Part Number 571-5745782-6
J4, J5, J6: Conn_01x02_Pin; PinHeader_1x02_P2.54mm_Vertical

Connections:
+15V: J3.9; also elsewhere on the board
-15V: J3.10; also elsewhere on the board
/1A_1: J3.8; also elsewhere on the board
/1A_2: J3.13; also elsewhere on the board
/1A_3: J3.3; also elsewhere on the board
/1B_1: J3.15; also elsewhere on the board
/1B_2: J3.6; also elsewhere on the board
/1B_3: J3.4; also elsewhere on the board
/2A_1: J3.7; also elsewhere on the board
/2A_2: J3.5; also elsewhere on the board
/2A_3: J3.2; also elsewhere on the board
/2B_1: J3.14; also elsewhere on the board
/2B_2: J3.12; also elsewhere on the board
/2B_3: J3.1; also elsewhere on the board
/AIN+: J5.2; also elsewhere on the board
/AIN-: J5.1; also elsewhere on the board
/BIAS_MOD: J6.2; also elsewhere on the board
/Connectors/BIAS: J2.7; also elsewhere on the board
/IOUT+: J4.2; also elsewhere on the board
/IOUT-: J4.1; also elsewhere on the board
/T_Amp+: J2.2; also elsewhere on the board
/T_Amp-: J2.1; also elsewhere on the board
/Z+X: J2.4; also elsewhere on the board
/Z+Y: J2.8; also elsewhere on the board
/Z-X: J2.5; also elsewhere on the board
/Z-Y: J2.15; also elsewhere on the board
GND: J2.3, J2.6, J2.9, J2.10, J2.11, J2.12, J2.13, J2.14, J3.11, J6.1; also elsewhere on the board
Shield: H1.1, J2.MH1, J2.MH2, J3.MH1, J3.MH2; also elsewhere on the board

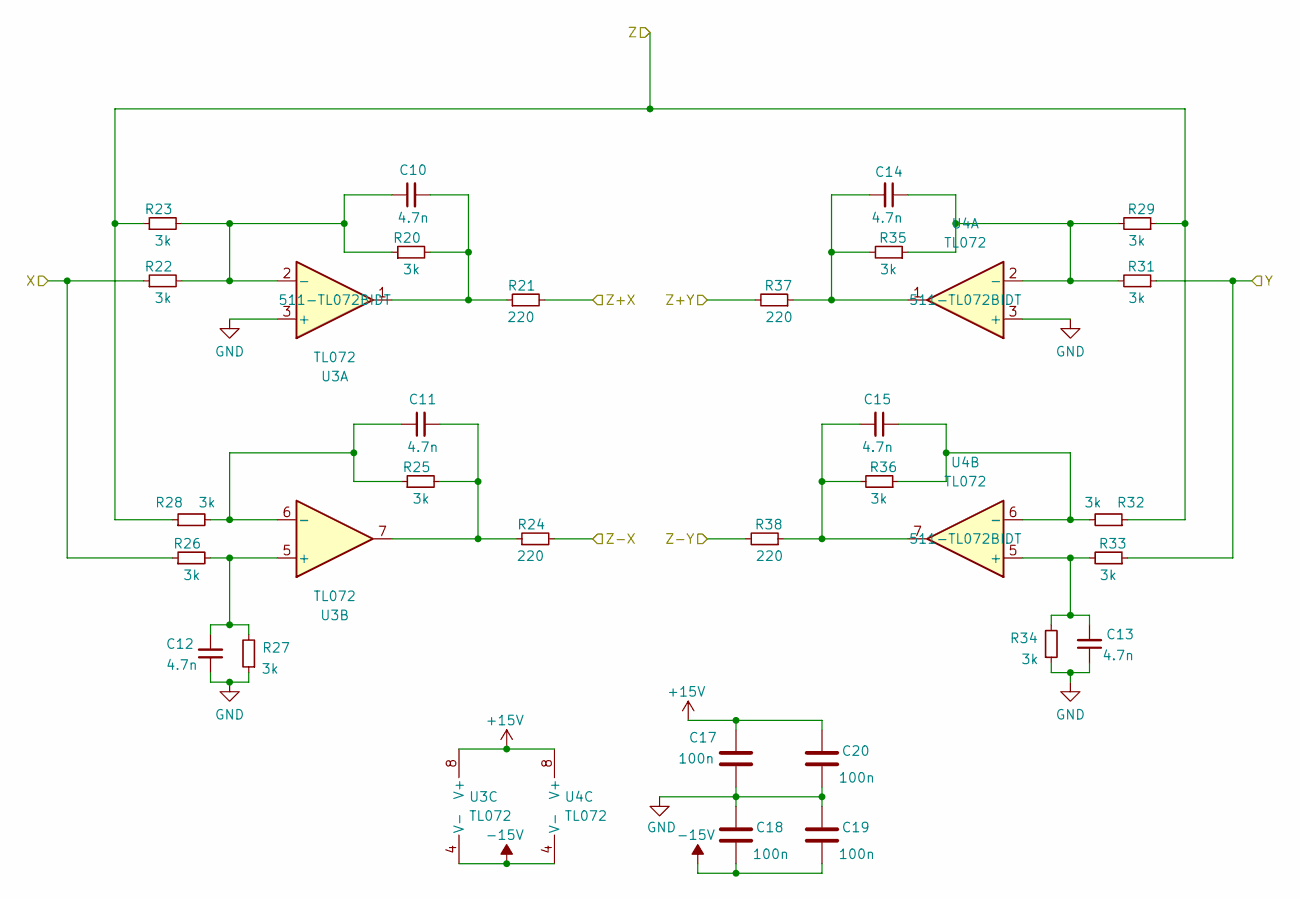
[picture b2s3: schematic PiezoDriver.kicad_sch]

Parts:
C10, C11, C12, C13, C14, C15: 4.7n; C_0805_2012Metric; Mouser Part Number 80-C0805C472J3GAUTO
C17, C18, C19, C20: 100n; C_0805_2012Metric; Mouser Part Number 80-C0805S104K1RACAUT; LCSC C14663
R20, R22, R23, R25, R26, R27, R28, R29, R31, R32, R33, R34, R35, R36: 3k; R_0805_2012Metric; Mouser Part Number 667-ERA-6AED302V
R21, R24, R37, R38: 220; R_0805_2012Metric; Mouser Part Number 279-CRGH0805F220R
U3, U4: TL072; SOIC-8-1EP_3.9x4.9mm_P1.27mm_EP2.29x3mm_ThermalVias; Mouser Part Number 511-TL072BIDT

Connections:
+15V: C17.1, C20.1, U3.8 (V+), U4.8 (V+); also elsewhere on the board
-15V: C18.2, C19.2, U3.4 (V-), U4.4 (V-); also elsewhere on the board
/X: R22.1, R26.1; also elsewhere on the board
/Y: R31.1, R33.1; also elsewhere on the board
/Z: R23.1, R28.1, R29.1, R32.1; also elsewhere on the board
/Z+X: R21.2; also elsewhere on the board
/Z+Y: R37.2; also elsewhere on the board
/Z-X: R24.2; also elsewhere on the board
/Z-Y: R38.2; also elsewhere on the board
GND: C12.1, C13.1, C17.2, C18.1, C19.1, C20.2, R27.1, R34.1, U3.3 (+), U4.3 (+); also elsewhere on the board
unnamed: C10.2, R20.2, R21.1, U3.1
unnamed: C11.2, R24.1, R25.2, U3.7
unnamed: C14.2, R35.2, R37.1, U4.1
unnamed: C15.2, R36.2, R38.1, U4.7
unnamed: C10.1, R20.1, R22.2, R23.2, U3.2 (-)
unnamed: C12.2, R26.2, R27.2, U3.5 (+)
unnamed: C11.1, R25.1, R28.2, U3.6 (-)
unnamed: C14.1, R29.2, R31.2, R35.1, U4.2 (-)
unnamed: C13.2, R33.2, R34.2, U4.5 (+)
unnamed: C15.1, R32.2, R36.1, U4.6 (-)

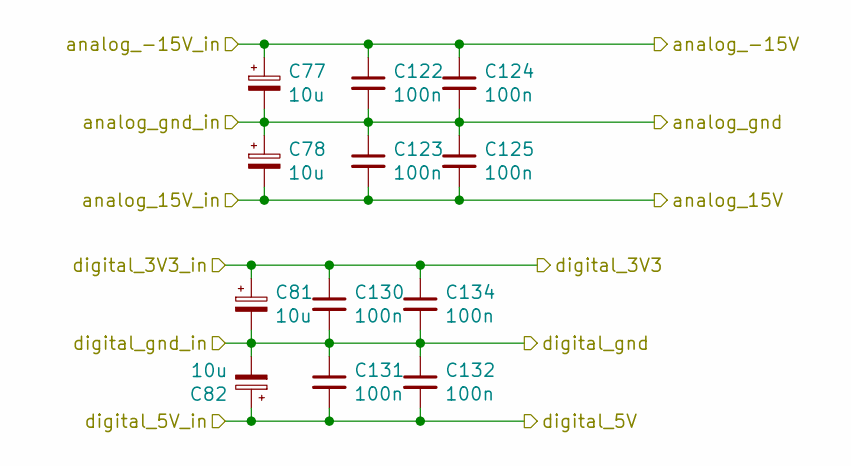
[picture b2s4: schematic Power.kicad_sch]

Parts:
C77, C78, C81, C82: 10u; CP_Radial_D5.0mm_P2.00mm; Mouser Part Number 710-860020472003
C122, C123, C124, C125, C130, C131, C132, C134: 100n; C_0805_2012Metric; Mouser Part Number 80-C0805S104K1RACAUT

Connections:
+3V3: C81.1, C130.1, C134.1; also elsewhere on the board
+5V: C82.1, C131.2, C132.2; also elsewhere on the board
+15V: C78.2, C123.2, C125.2; also elsewhere on the board
-15V: C77.1, C122.1, C124.1; also elsewhere on the board
GND: C77.2, C78.1, C81.2, C82.2, C122.2, C123.1, C124.2, C125.1, C130.2, C131.1, C132.1, C134.2; also elsewhere on the board

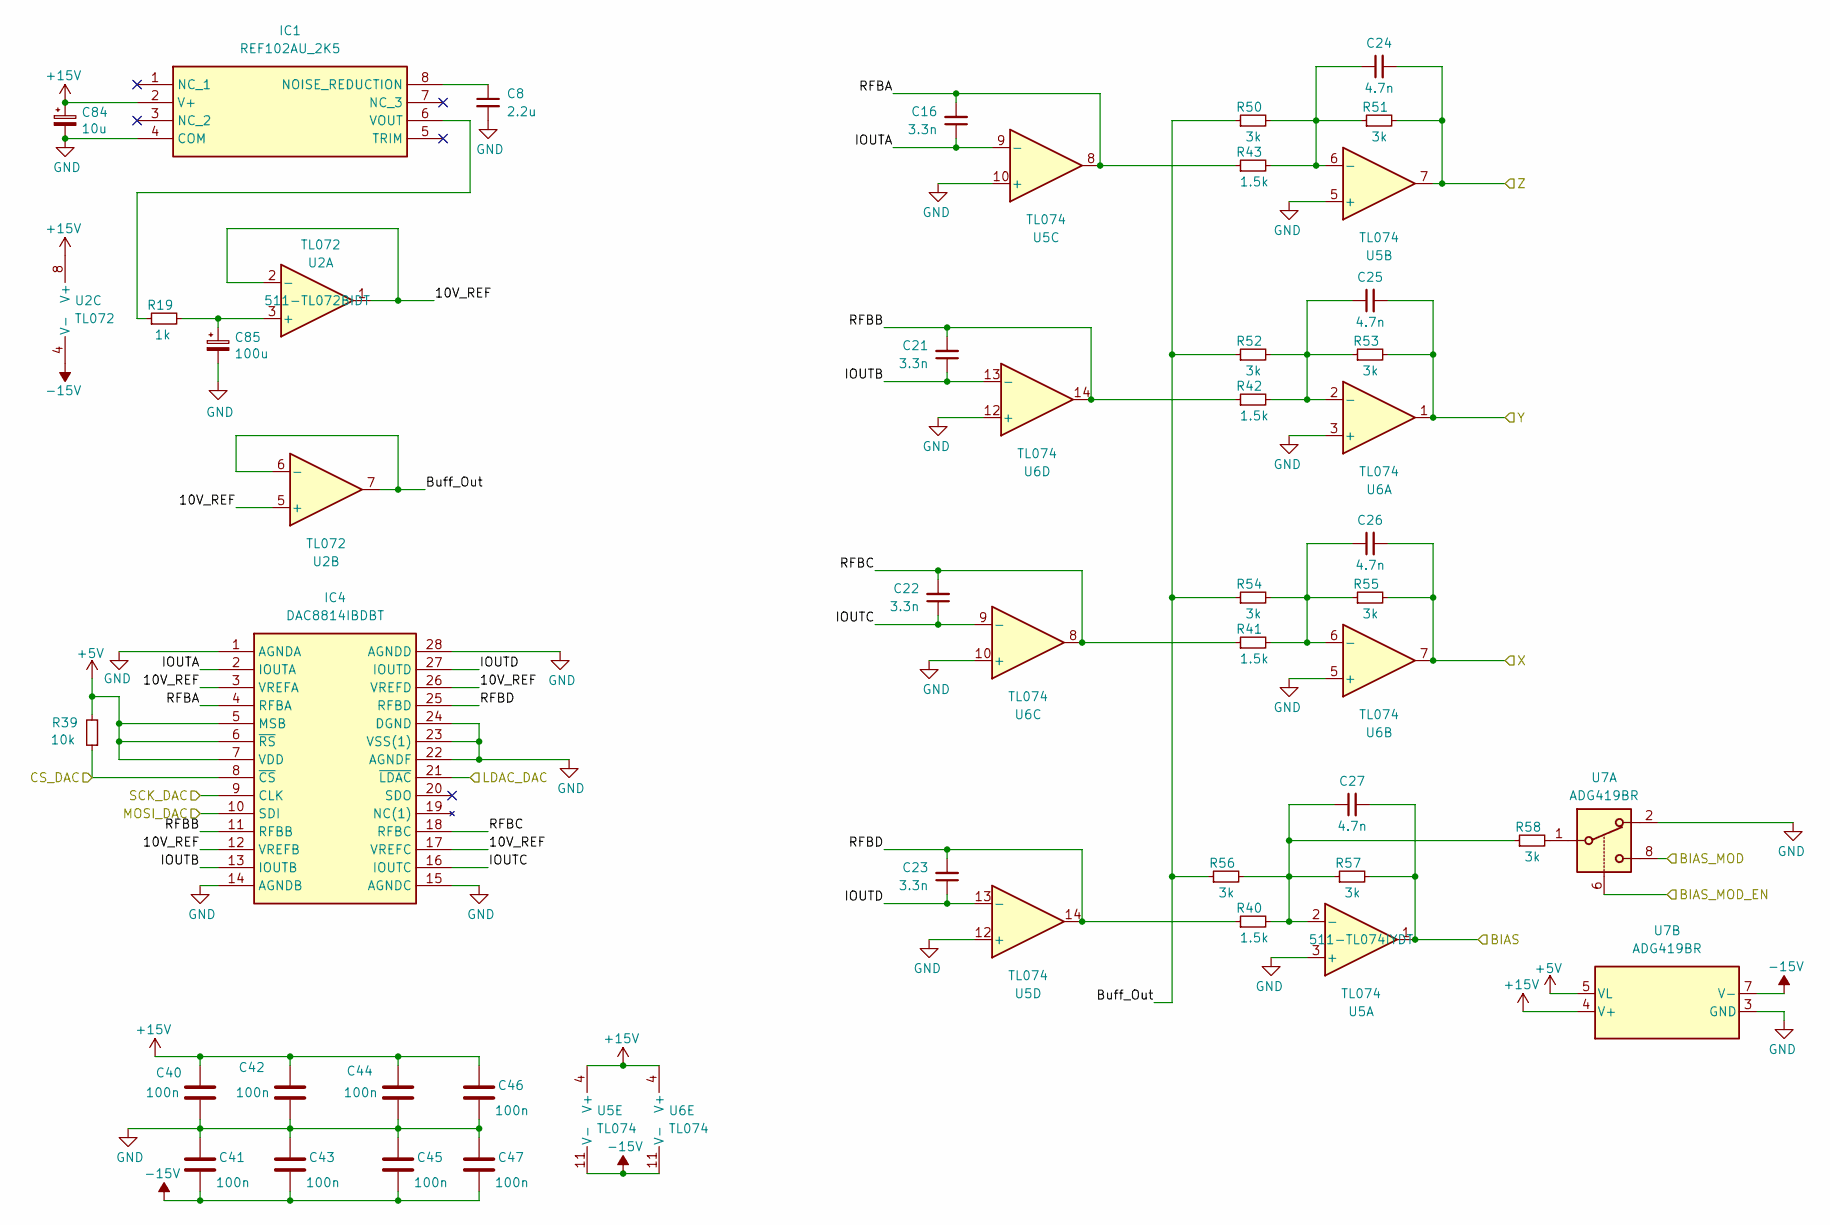
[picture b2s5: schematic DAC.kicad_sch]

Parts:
C8: 2.2u; C_0805_2012Metric; Mouser Part Number 80-C0805C225K4R3123
C16, C21, C22, C23: 3.3n; C_0805_2012Metric; Mouser Part Number 80-C0805C332KCR
C24, C25, C26, C27: 4.7n; C_0805_2012Metric; Mouser Part Number 80-C0805C472J3GAUTO
C40, C41, C42, C43, C44, C45, C46, C47: 100n; C_0805_2012Metric; Mouser Part Number 80-C0805S104K1RACAUT; LCSC C14663
C84: 10u; CP_Radial_D5.0mm_P2.00mm; Mouser Part Number 710-860020472003
C85: 100u; CP_Radial_D6.3mm_P2.50mm; Mouser Part Number 80-ESW107M016AE3EA
IC1: REF102AU_2K5; SOIC127P600X175-8N; Mouser Part Number 595-REF102AU/2K5
IC4: DAC8814IBDBT; SOP65P780X200-28N; Mouser Part Number 595-DAC8814IBDBT
R19: 1k; R_0805_2012Metric; Mouser Part Number 755-ESR10EZPJ102
R39: 10k; R_0805_2012Metric; Mouser Part Number 755-ESR10EZPD1002
R40, R41, R42, R43: 1.5k; R_0805_2012Metric; Mouser Part Number 755-ESR10EZPF1501
R50, R51, R52, R53, R54, R55, R56, R57, R58: 3k; R_0805_2012Metric; Mouser Part Number 667-ERA-6AED302V
U2: TL072; SOIC-8-1EP_3.9x4.9mm_P1.27mm_EP2.29x3mm_ThermalVias; Mouser Part Number 511-TL072BIDT
U5, U6: TL074; SOIC-14_3.9x8.7mm_P1.27mm; Mouser Part Number 511-TL074IYDT
U7: ADG419BR; SOIC-8_3.9x4.9mm_P1.27mm; Mouser Part Number 584-ADG419BRZ-R

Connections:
+5V: IC4.5 (MSB), IC4.6 (~RS), IC4.7 (VDD), R39.2, U7.5 (VL); also elsewhere on the board
+15V: C40.1, C42.1, C44.1, C46.1, C84.1, IC1.2 (V+), U2.8 (V+), U5.4 (V+), U6.4 (V+), U7.4 (V+); also elsewhere on the board
-15V: C41.2, C43.2, C45.2, C47.2, U2.4 (V-), U5.11 (V-), U6.11 (V-), U7.7 (V-); also elsewhere on the board
/BIAS_MOD: U7.8; also elsewhere on the board
/BIAS_MOD_EN: U7.6; also elsewhere on the board
/CS_DAC: IC4.8 (~CS), R39.1; also elsewhere on the board
/Connectors/BIAS: C27.2, R57.2, U5.1; also elsewhere on the board
/DAC/10V_REF: IC4.3 (VREFA), IC4.12 (VREFB), IC4.17 (VREFC), IC4.26 (VREFD), U2.1, U2.2 (-), U2.5 (+)
/DAC/Buff_Out: R50.1, R52.1, R54.1, R56.1, U2.6 (-), U2.7
/DAC/IOUTA: C16.1, IC4.2 (IOUTA), U5.9 (-)
/DAC/IOUTB: C21.1, IC4.13 (IOUTB), U6.13 (-)
/DAC/IOUTC: C22.1, IC4.16 (IOUTC), U6.9 (-)
/DAC/IOUTD: C23.1, IC4.27 (IOUTD), U5.13 (-)
/DAC/RFBA: C16.2, IC4.4 (RFBA), R43.1, U5.8
/DAC/RFBB: C21.2, IC4.11 (RFBB), R42.1, U6.14
/DAC/RFBC: C22.2, IC4.18 (RFBC), R41.1, U6.8
/DAC/RFBD: C23.2, IC4.25 (RFBD), R40.1, U5.14
/LDAC_DAC: IC4.21 (~LDAC); also elsewhere on the board
/MOSI_DAC: IC4.10 (SDI); also elsewhere on the board
/SCK_ADC: IC4.9 (CLK); also elsewhere on the board
/X: C26.2, R55.2, U6.7; also elsewhere on the board
/Y: C25.2, R53.2, U6.1; also elsewhere on the board
/Z: C24.2, R51.2, U5.7; also elsewhere on the board
GND: C8.2, C40.2, C41.1, C42.2, C43.1, C44.2, C45.1, C46.2, C47.1, C84.2, C85.2, IC1.4 (COM), IC4.1 (AGNDA), IC4.14 (AGNDB), IC4.15 (AGNDC), IC4.22 (AGNDF), IC4.23 (VSS(1)), IC4.24 (DGND), IC4.28 (AGNDD), U5.3 (+), U5.5 (+), U5.10 (+), U5.12 (+), U6.3 (+), U6.5 (+), U6.10 (+), U6.12 (+), U7.2, U7.3 (GND); also elsewhere on the board
unnamed: C8.1, IC1.8 (NOISE_REDUCTION)
unnamed: IC1.6 (VOUT), R19.1
unnamed: R58.2, U7.1
unnamed: C85.1, R19.2, U2.3 (+)
unnamed: C27.1, R40.2, R56.2, R57.1, R58.1, U5.2 (-)
unnamed: C24.1, R43.2, R50.2, R51.1, U5.6 (-)
unnamed: C25.1, R42.2, R52.2, R53.1, U6.2 (-)
unnamed: C26.1, R41.2, R54.2, R55.1, U6.6 (-)
